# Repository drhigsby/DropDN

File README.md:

# DropDN
 A 9u wide ortholinear keyboard designed around a modified colemak layout

http://www.keyboard-layout-editor.com/#/gists/a7e25f51ee7695ad3ce9d2ccd07c6cc2

https://i.imgur.com/tiWlH6h.png

Required Hardware:

-6x 10mm M3 standoffs

-12x 6mm or 8mm M3 screws

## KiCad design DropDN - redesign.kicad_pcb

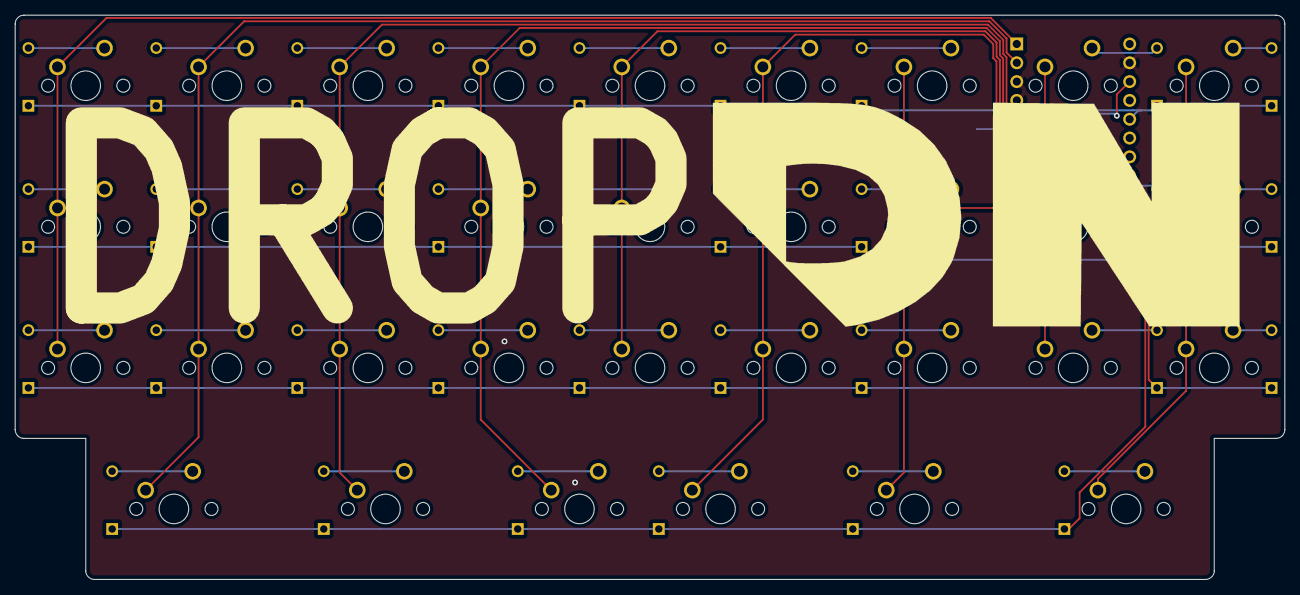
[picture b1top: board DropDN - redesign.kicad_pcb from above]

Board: 2 copper layers, 171.5 x 76.2 mm, 68 parts (1 on the bottom side), 48 nets.

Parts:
D1, D2, D3, D4, D5, D6, D7, D8, D9, D10, D11, D12, D13, D14, D15, D16, D17, D18, D19, D20, D21, D22, D23, D24, D25, D26, D27, D28, D29, D30, D31, D32, D33: D_Small; Diode-Hybrid-Back
MX1, MX2, MX3, MX4, MX5, MX6, MX7, MX8, MX9, MX10, MX11, MX12, MX13, MX14, MX15, MX16, MX17, MX18, MX19, MX20, MX21, MX22, MX23, MX24, MX25, MX26, MX27, MX30, MX31: MX-NoLED; MXOnly-1U-NoLED
MX28, MX33: MX-NoLED; MXOnly-1.25U-NoLED
MX29, MX32: MX-NoLED; MXOnly-1.75U-NoLED
PM1: ProMicro; ArduinoProMicro
RESET1: reset; SKQG-1155865

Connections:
GND: PM1.3, PM1.4, PM1.23, RESET1.2
unnamed: D1.2, MX1.2
unnamed: D2.2, MX2.2
unnamed: D3.2, MX3.2
unnamed: D4.2, MX4.2
unnamed: D5.2, MX5.2
unnamed: D6.2, MX6.2
unnamed: D7.2, MX7.2
unnamed: D8.2, MX8.2
unnamed: D9.2, MX9.2
unnamed: D10.2, MX10.2
unnamed: D11.2, MX11.2
unnamed: D12.2, MX12.2
unnamed: D13.2, MX13.2
unnamed: D14.2, MX14.2
unnamed: D15.2, MX15.2
unnamed: D16.2, MX16.2
unnamed: D17.2, MX17.2
unnamed: D18.2, MX18.2
unnamed: D19.2, MX19.2
unnamed: D20.2, MX20.2
unnamed: D21.2, MX21.2
unnamed: D22.2, MX22.2
unnamed: D23.2, MX23.2
unnamed: D24.2, MX24.2
unnamed: D25.2, MX25.2
unnamed: D26.2, MX26.2
unnamed: D27.2, MX27.2
unnamed: D28.2, MX28.2
unnamed: D29.2, MX29.2
unnamed: D30.2, MX30.2
unnamed: D31.2, MX31.2
unnamed: D32.2, MX32.2
unnamed: D33.2, MX33.2
RST: PM1.22, RESET1.1
c1: MX1.1, MX10.1, MX19.1, PM1.1
c2: MX2.1, MX11.1, MX20.1, MX28.1, PM1.2
c3: MX3.1, MX12.1, MX21.1, MX29.1, PM1.5
c4: MX4.1, MX13.1, MX22.1, MX30.1, PM1.6
c5: MX5.1, MX14.1, MX23.1, PM1.7
c6: MX6.1, MX15.1, MX24.1, MX31.1, PM1.8
c7: MX7.1, MX16.1, MX25.1, MX32.1, PM1.9
c8: MX8.1, MX17.1, MX26.1, PM1.10
c9: MX9.1, MX18.1, MX27.1, MX33.1, PM1.16
r1: D1.1, D2.1, D3.1, D4.1, D5.1, D6.1, D7.1, D8.1, D9.1, PM1.20
r2: D10.1, D11.1, D12.1, D13.1, D14.1, D15.1, D16.1, D17.1, D18.1, PM1.13
r3: D19.1, D20.1, D21.1, D22.1, D23.1, D24.1, D25.1, D26.1, D27.1, PM1.15
r4: D28.1, D29.1, D30.1, D31.1, D32.1, D33.1, PM1.14

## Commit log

2021-06-02 whole buncha changes
2021-06-02 few org changes
2021-06-02 idk, some changes maybe
2021-07-08 added a 4u footprint
2021-07-20 fixed reset button issue
2021-07-20 bunch of updates
    1) Made 3 small modifications to the case design based on the proto:
    a) more clearance for switches on top layer
    b) actual clearance for usb port on PM
    c) closed the compression layer for aesthetics
    2) made alterations to the PCB silk
    3) fixed an issue with the reset switch pads that prevented a physically soldered reset switch from working
2021-07-20 more updates
    updated middle layer and bottom layer corners on SAS case
2021-07-21 updated case files
2021-08-24 huge overhaul
